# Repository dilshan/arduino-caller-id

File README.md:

# Arduino based telephone caller ID display unit

This project is a simple Caller ID (CLI) decoder made using the [Arduino UNO](https://www.arduino.cc/en/Main/ArduinoBoardUno) and a custom-made [HT9032D](https://www.holtek.com/documents/10179/116711/HT9032C_Dv170.pdf) module.

## HT9032D module

The HT9032D module design files are available at *[/ht9032d-module](https://github.com/dilshan/arduino-caller-id/tree/main/ht9032d-module) directory*. *Gerber files* for PCB production are in the [Release](https://github.com/dilshan/arduino-caller-id/releases) section of this repository.

The HT9032D module consists of standard through-hole type components. No special soldering equipment is needed to assemble this module.

The following table lists all the components needed to complete the HT9032D module.

| Designator | Value                                                                                                                         | Quantity |
|------------|-------------------------------------------------------------------------------------------------------------------------------|----------|
| C1, C3     | 0.01μF / 400V                                                                                                                 | 2        |
| C2         | 0.1μF / 50V                                                                                                                   | 1        |
| C4, C5     | 33pF                                                                                                                          | 2        |
| C6, C7     | 0.22μF / 400V                                                                                                                 | 2        |
| D1         | [2W10](https://octopart.com/2w10g-e4%2F51-vishay-42173035) Bridge rectifier                                                   | 1        |
| R1, R2     | 200KΩ (¼W Carbon film resistor - 5%)                                                                                          | 2        |
| R3         | 22KΩ (¼W Carbon film resistor - 5%)                                                                                           | 1        |
| R4         | 10MΩ (¼W Carbon film resistor - 5%)                                                                                           | 1        |
| R5         | 470KΩ (¼W Carbon film resistor - 5%)                                                                                          | 1        |
| R6         | 18KΩ (¼W Carbon film resistor - 5%)                                                                                           | 1        |
| R7         | 15KΩ (¼W Carbon film resistor - 5%)                                                                                           | 1        |
| U1         | [HT9032D](https://octopart.com/ht9032d-holtek-20921619) (DIP-8)                                                               | 1        |
| Y1         | 3.58MHz (HC49) Crystal                                                                                                        | 1        |
| J1         | RJ11 / 6P6C, 6-pin, right angle, PCB socket ([Molex 52018-6616](https://octopart.com/52018-6616-molex-7664937) or equivalent) | 1        |
| J2         | 5-pin 2.54mm Pin header                                                                                                       | 1        |

## Assembling the Caller ID display unit

The following components and modules are required to assemble the call ID display unit.

1.  *Assembled HT9032D module*
2.  *Arduino UNO* board
3.  [16x2 HD44780 character LCD panel](https://www.adafruit.com/product/181)
4.  [2N3904](https://octopart.com/2n3904tf-on+semiconductor-84408862) (or equivalent NPN) Transistor
5.  50KΩ Trimpot (RM-063 or equivalent)
6.  560Ω (¼W) resistor
7.  22KΩ (¼W) resistor
8.  Few [mini/small breadboard(s)](https://www.adafruit.com/product/65)

Both *[pictorial](https://github.com/dilshan/arduino-caller-id/blob/main/schematic/arduino-uno-layout.jpg)* and *[symbolic](https://github.com/dilshan/arduino-caller-id/blob/main/schematic/arduino-uno-caller-id.pdf)* wiring diagrams are provided to minimize the complexity of assembly.

The Arduino sketch required for this caller ID is available [here](https://github.com/dilshan/arduino-caller-id/blob/main/arduino-sketch/arduino-callerid/arduino-callerid.ino).

The current version of this caller ID decoder sketch can handle the *caller line ID*, *name*, and *date/time* MDMF (*Multiple Data Message Format*) packet IDs only.

## License

All the source codes in this repository are released under the terms of the [MIT License](https://github.com/dilshan/arduino-caller-id/blob/main/LICENSE). The *HT9032D module* design files are released under the [CERN-OHL-W Version 2.0](https://ohwr.org/cern_ohl_w_v2.txt) License.

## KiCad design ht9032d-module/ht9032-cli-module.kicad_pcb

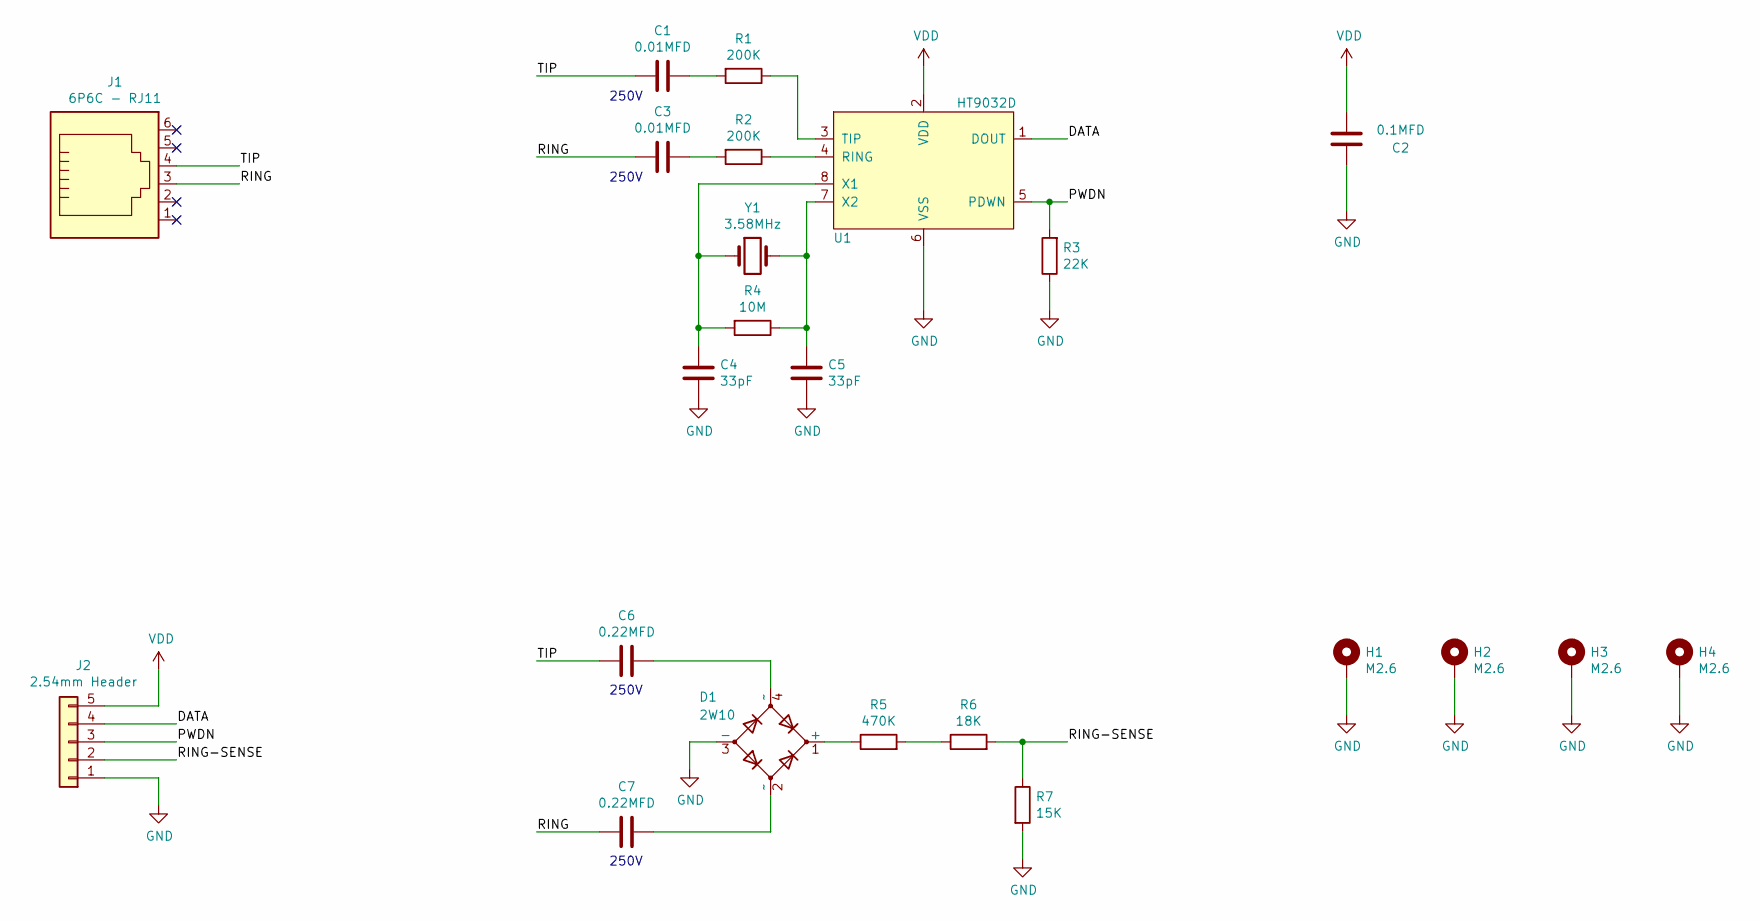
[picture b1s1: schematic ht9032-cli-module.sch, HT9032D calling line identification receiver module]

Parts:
C1, C3: 0.01MFD; C_Disc_D10.5mm_W5.0mm_P5.00mm
C2: 0.1MFD; C_Rect_L9.0mm_W4.2mm_P7.50mm_MKT
C4, C5: 33pF; C_Disc_D3.8mm_W2.6mm_P2.50mm
C6, C7: 0.22MFD; C_Rect_L11.0mm_W7.3mm_P10.00mm_MKT
D1: 2W10; Diode_Bridge_Round_D9.0mm
H1, H2, H3, H4: M2.6; MountingHole_2.7mm_Pad
J1: 6P6C - RJ11; RJ25_Wayconn_MJEA-660X1_Horizontal
J2: 2.54mm Header; PinHeader_1x05_P2.54mm_Vertical
R1, R2: 200K; R_Axial_DIN0207_L6.3mm_D2.5mm_P10.16mm_Horizontal
R3: 22K; R_Axial_DIN0207_L6.3mm_D2.5mm_P10.16mm_Horizontal
R4: 10M; R_Axial_DIN0207_L6.3mm_D2.5mm_P10.16mm_Horizontal
R5: 470K; R_Axial_DIN0207_L6.3mm_D2.5mm_P10.16mm_Horizontal
R6: 18K; R_Axial_DIN0207_L6.3mm_D2.5mm_P10.16mm_Horizontal
R7: 15K; R_Axial_DIN0207_L6.3mm_D2.5mm_P10.16mm_Horizontal
U1: HT9032D; DIP-8_W7.62mm_LongPads
Y1: 3.58MHz; Crystal_HC49-U_Vertical

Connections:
/DATA: J2.4, U1.1 (DOUT)
/PWDN: J2.3, R3.2, U1.5 (PDWN)
/RING: C3.2, C7.2, J1.3
/RING-SENSE: J2.2, R6.2, R7.1
/TIP: C1.2, C6.2, J1.4
GND: C2.1, C4.2, C5.2, D1.3 (-), H1.1, H2.1, H3.1, H4.1, J2.1, R3.1, R7.2, U1.6 (VSS)
unnamed: C1.1, R1.2
unnamed: C3.1, R2.2
unnamed: C4.1, R4.2, U1.8 (X1), Y1.1
unnamed: C5.1, R4.1, U1.7 (X2), Y1.2
unnamed: C6.1, D1.4 (~~)
unnamed: C7.1, D1.2 (~~)
unnamed: D1.1 (+), R5.1
unnamed: R1.1, U1.3 (TIP)
unnamed: R2.1, U1.4 (RING)
unnamed: R5.2, R6.1
VDD: C2.2, J2.5, U1.2 (VDD)

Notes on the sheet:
250V

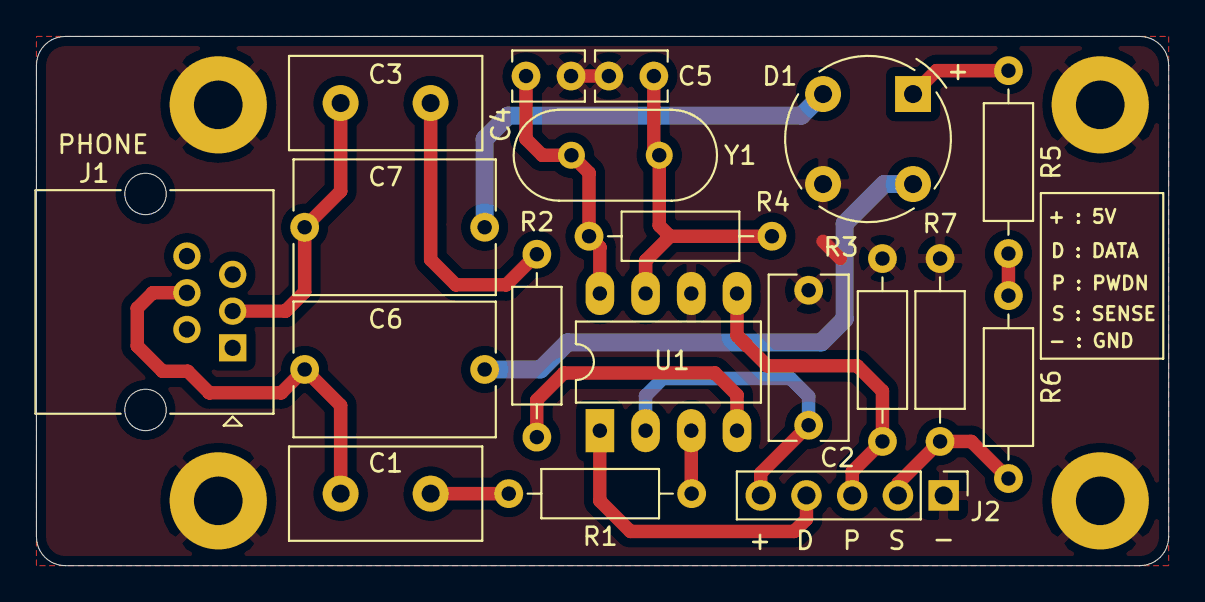
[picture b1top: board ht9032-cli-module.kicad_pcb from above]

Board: 2 copper layers, 62.9 x 29.4 mm, 23 parts (0 on the bottom side), 17 nets.

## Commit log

2021-08-12 Initial version of HT9032D module design files, Arduino sketch and layout files.
2021-08-12 Initial version of readme.md file.
2021-08-12 Add resource images of HT9032D module and finished CLI unit prototype.
2021-08-12 Update resource links in readme.md file.
2021-08-13 Initial version of GitHub CI Workflow.
2021-08-13 Update Arduino CLI version in workflow configuration.
2021-08-13 Add LiquidCrystal library setup into Workflow configuration.
2021-08-13 Add CI workflow status badge into readme.md.
2021-08-13 Update links in readme.md file.
2021-08-13 :movie_camera: Add YouTube video link to the readme.md file.
2021-08-13 Add YouTube video thumbnail.
2021-08-13 :movie_camera: Add YouTube tumbnail as cover image.

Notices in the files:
ht9032d-module/ht9032-cli-module.kicad_pcb:
Licensed under CERN-OHL-W Version 2.0
CERN-OHL-W V2.0
